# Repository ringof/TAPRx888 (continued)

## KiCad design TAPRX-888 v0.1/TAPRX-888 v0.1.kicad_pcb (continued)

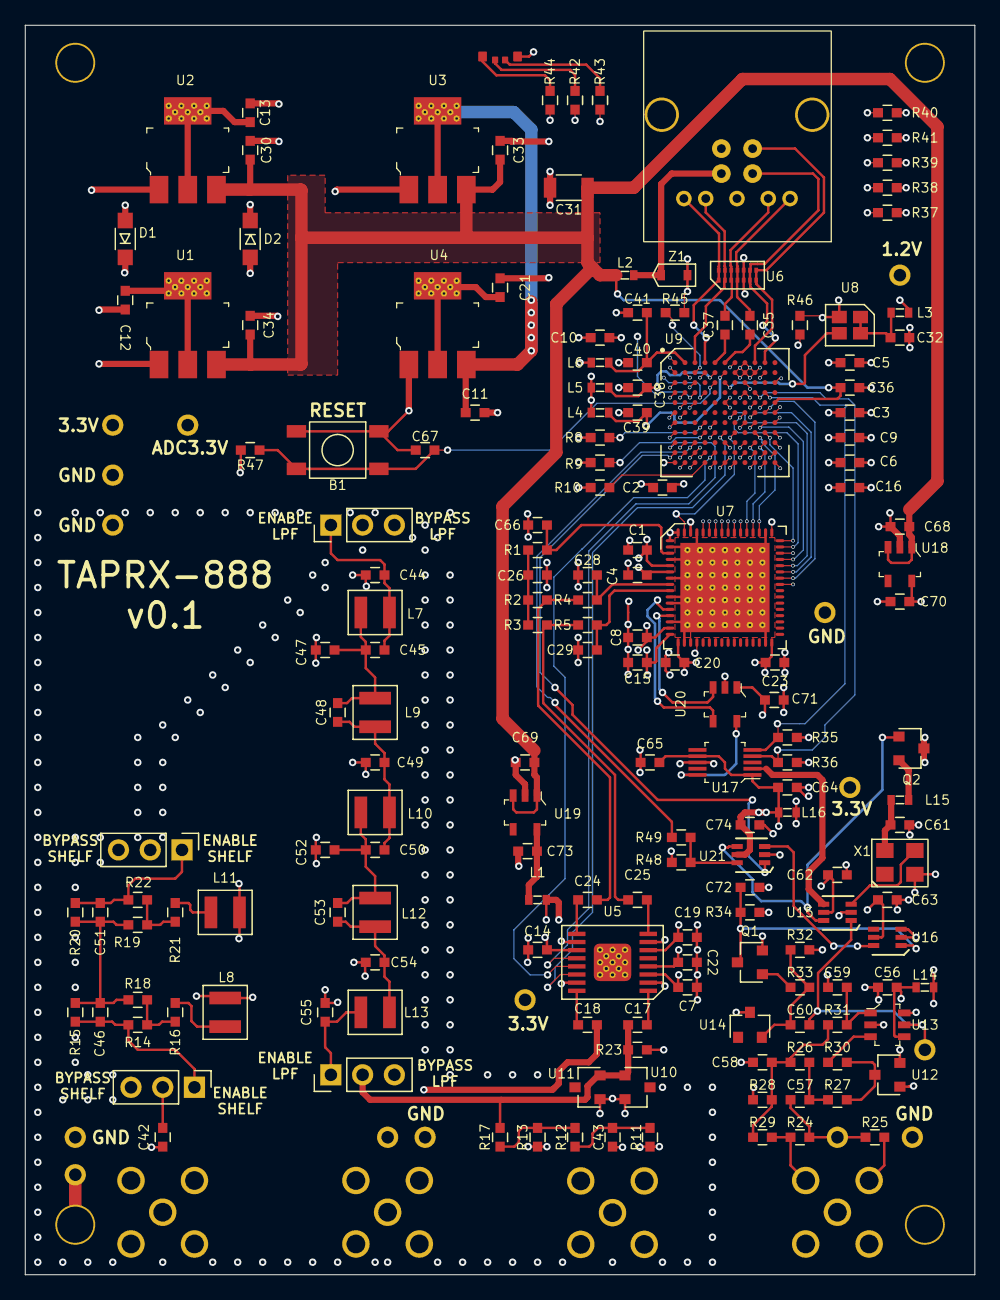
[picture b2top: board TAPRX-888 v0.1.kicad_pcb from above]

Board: 6 copper layers, 76.0 x 100.0 mm, 194 parts (1 on the bottom side), 123 nets.

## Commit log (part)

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2026-05-19 Initial files from Turn Island Systems repository
    only the TAPRx888 files
2026-05-19 add test points (SCH only) for UART, GPIF, and RF fs-clk option
2026-06-03 Add files via upload
    Schematic and layout fixes per issues 1-11
2026-06-03 split out the KiCad files into their own folder. Please use THIS!
    No need to use a zip file or separate folders for what Git manages already
2026-06-03 rename kicad files with version numbers in the names
    not needed
2026-06-03 add Claude's review of the current work
    Claude's review
2026-06-03 move review from KiCad folder to main folder
    Belongs in the main folder...
2026-06-03 another review by Claude
    Claude rev 3 review
2026-06-04 Add files via upload
    v0.3a has clean ERC. No design changes required, just flags, etc.
2026-06-04 acquire Pauls' latest work
    in zip file 0.3a.zip. took its files and put into TAPRX-888 KiCad, renaming them.
    Moved old work to a new folder, WB6CXC previous work.
2026-06-04 add a Reference manuals folder
    Put in relevant chip datasheets and appnotes
    put the .history folder on .gitignore
    commit the new .gitignore
2026-06-04 Enhance README with additional features
    Added details about SPI boot prom configuration.
2026-06-07 v0.4 changes
    all in a separate folder
2026-06-07 reorg to put into main directory
    moved paul's v0.4 work into the main folder
2026-06-07 Adding local KiCad symbol and footprint libraries to project
    Adding local KiCad symbol and footprint libraries to project
2026-06-08 Updated via and relief dimensions
    Dimensions based on JLCPCB documentation, but using 0.15mm hole and 0.25mm clearance minimums.
2026-06-08 cleanup BGA dimensions
    tighter reliefs under BPA, relaxed elsewhere,
2026-06-09 another double check
2026-06-09 add TAPRX-888-backups to ignore
    don't need to accumulate zip files in the repository.
2026-06-09 remove zip backups
    hopefully marked correctly in a .gitignore
2026-06-16 add proper si5315 ref manual, augmented BOM
    had to improve the BOM to get the MFG and MPN for each of the 'LCSC part' items. needed for AdvancedPCB to quote. had the si5357 manual, which is not the si5351 manual.
2026-06-18 Update README.md formatting and content references
    ask people to look at the TAPRX-888 KiCad folder
2026-06-22 stamp schematic title block with GIT_HASH
2026-06-22 docs: point README downloads at 51a552b build [skip ci]
2026-06-26 Updated ADC component data, fixed KiCad v10 zone issue
    ADC name and LCSC # updated
    KiCad v10 DRC changes - zone overlap and priority check failed (board OK, just DRC issue). Fixed DRC by merging zones.
